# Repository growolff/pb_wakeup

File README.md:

# pb_wakeup
power bank wake up circuit

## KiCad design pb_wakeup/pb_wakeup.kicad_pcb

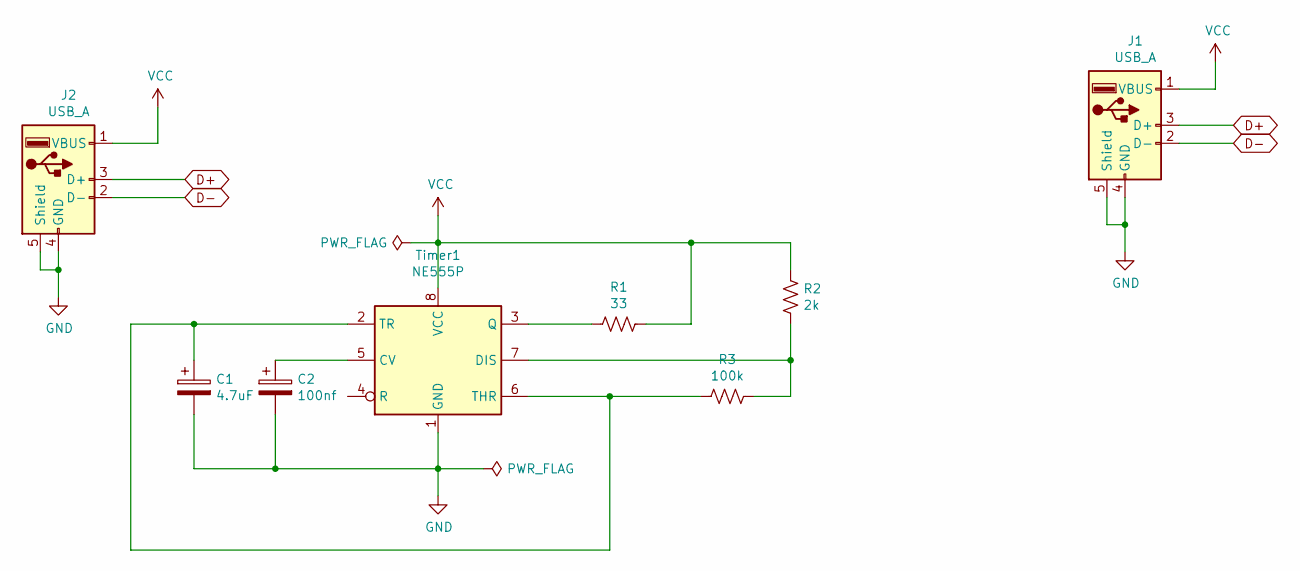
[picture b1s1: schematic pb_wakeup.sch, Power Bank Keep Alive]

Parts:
C1: 4.7uF; CP_Radial_D5.0mm_P2.50mm
C2: 100nf; CP_Radial_D5.0mm_P2.50mm
J1: USB_A; USB_A_Molex_67643_Horizontal
J2: USB_A; USB_A_CONNFLY_DS1095-WNR0
R1: 33; R_1206_3216Metric
R2: 2k; R_1206_3216Metric
R3: 100k; R_1206_3216Metric
Timer1: NE555P; DIP-8_W7.62mm

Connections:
D+: J1.3 (D+), J2.3 (D+)
D-: J1.2 (D-), J2.2 (D-)
GND: C1.2, C2.2, J1.4 (GND), J1.5 (Shield), J2.4 (GND), J2.5 (Shield), Timer1.1 (GND)
unnamed: C1.1, R3.1, Timer1.2 (TR), Timer1.6 (THR)
unnamed: C2.1, Timer1.5 (CV)
unnamed: R1.2, Timer1.3 (Q)
unnamed: R2.2, R3.2, Timer1.7 (DIS)
VCC: J1.1 (VBUS), J2.1 (VBUS), R1.1, R2.1, Timer1.8 (VCC)

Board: 2 copper layers, 8 parts (0 on the bottom side), 8 nets, no tracks yet.

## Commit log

2021-11-29 kicad files
